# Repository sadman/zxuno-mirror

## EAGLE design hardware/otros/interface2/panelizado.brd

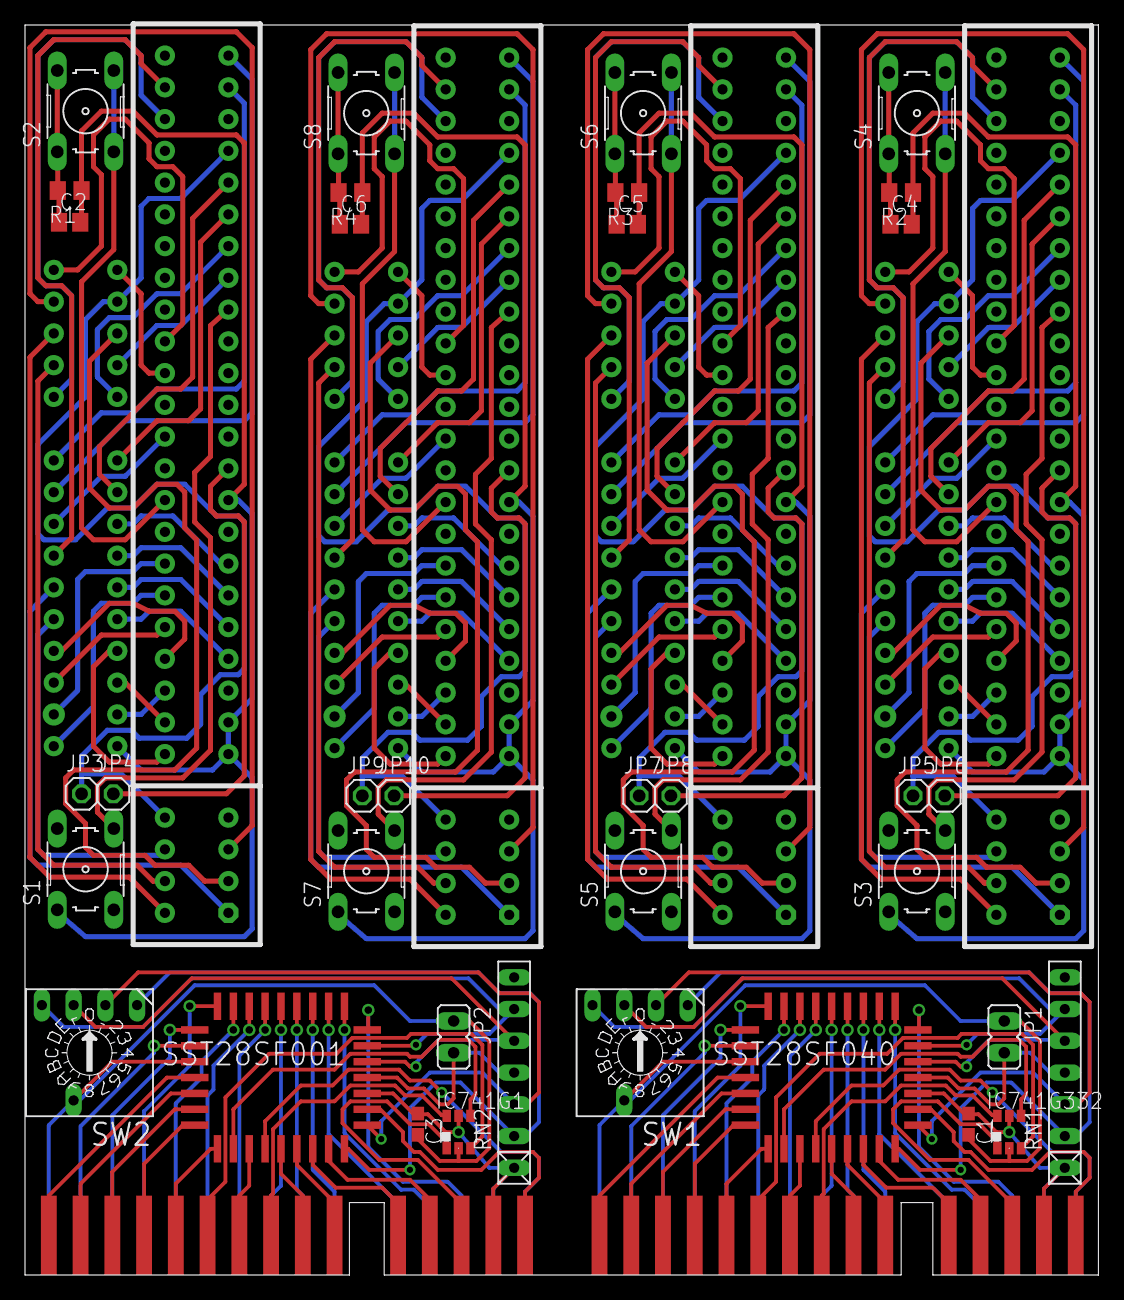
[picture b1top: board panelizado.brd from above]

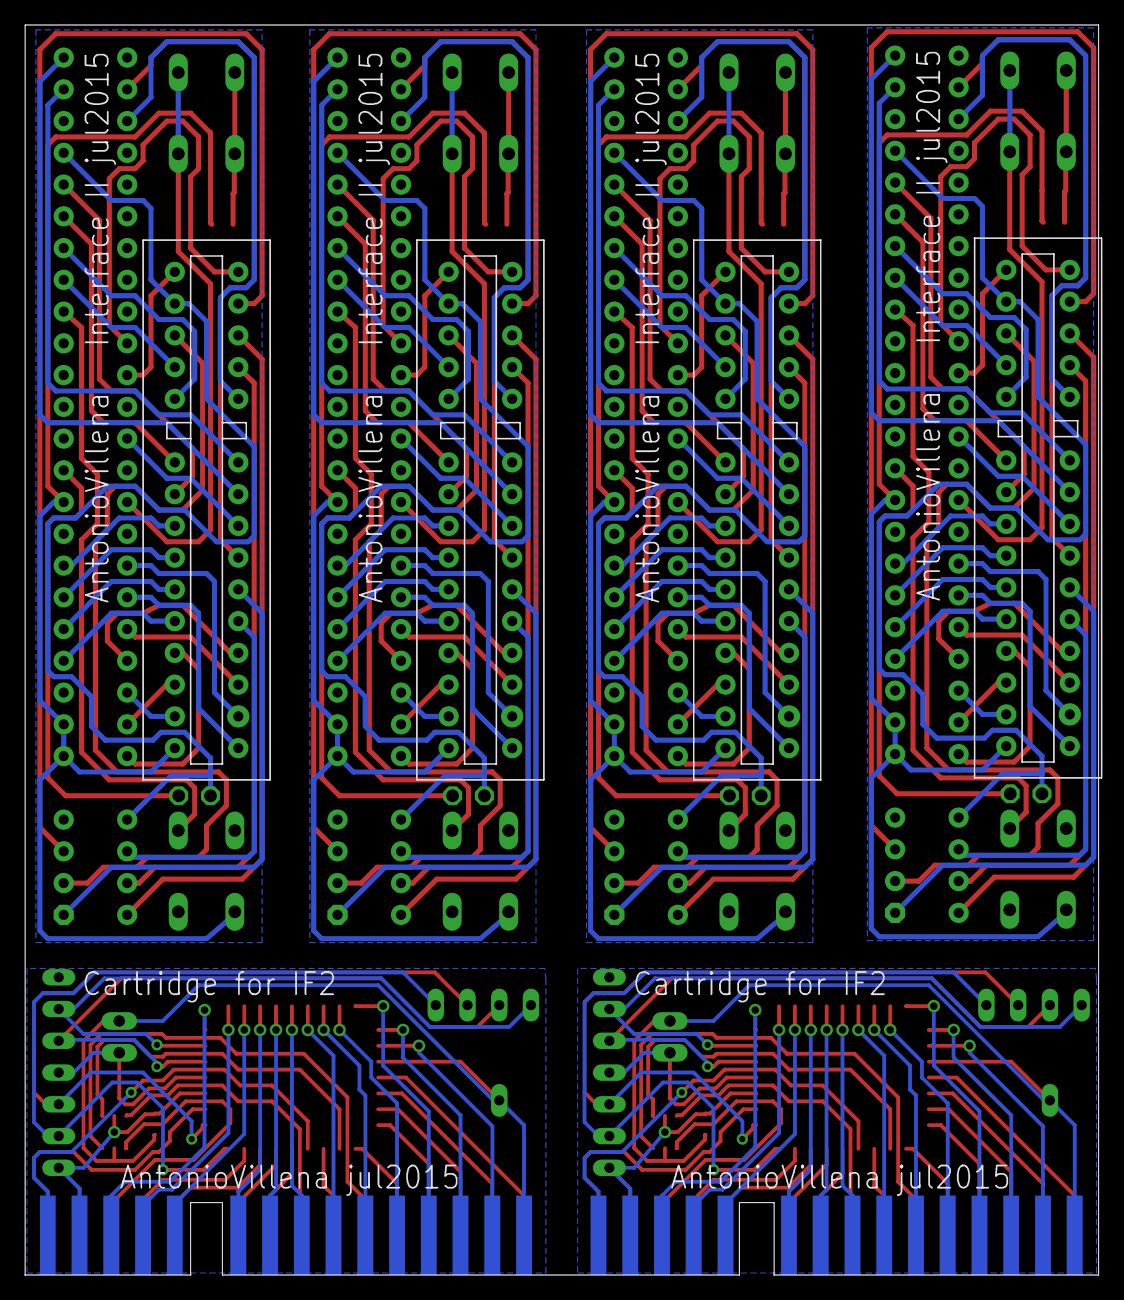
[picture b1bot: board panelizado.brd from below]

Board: 2 copper layers, 85.9 x 100.0 mm, 46 parts (4 on the bottom side), 206 nets.

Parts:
C1, C3: C0603
C2, C4, C5, C6: 4.7uF; C0805
IC741G1, IC741G332: DBV_R-PDSO-G6
JP1, JP2: JP1
JP3, JP4, JP5, JP6, JP7, JP8, JP9, JP10: 1X01
R1, R2, R3, R4: 1K; R0805
RN1, RN2: RN-7
S1, S2, S3, S4, S5, S6, S7, S8: B3F-10XX
SST28SF001, SST28SF040: PLCC32R
SW1, SW2: SW-C16
U$1, U$4: IF2BUS; BUS_CARTUCHO_IF2
U$2, U$6, U$8, U$10: ZX_CARTRIDGE
U$3, U$5, U$7, U$9: 2X28_SPE

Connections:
A0: SST28SF040.12, U$1.A0
A1: SST28SF040.11, U$1.A1
A2: SST28SF040.10, U$1.A2
A3: SST28SF040.9, U$1.A3
A4: SST28SF040.8, U$1.A4
A5: SST28SF040.7, U$1.A5
A6: SST28SF040.6, U$1.A6
A7: SST28SF040.5, U$1.A7
A8: SST28SF040.27, U$1.A8
A9: SST28SF040.26, U$1.A9
A10: SST28SF040.23, U$1.A10
A11: SST28SF040.25, U$1.A11
A12: SST28SF040.4, U$1.A12
A13: SST28SF040.28, U$1.A13
A14: IC741G332.3, U$1.A14
A15: IC741G332.1, U$1.A15
A16: U$2.A14, U$3.A1
A17: U$2.A10, U$3.B27
A18: U$2.A11, U$3.A28
A19: U$2.A9, U$3.A27
A20: U$2.A8, U$3.B26
A21: U$2.A13, U$3.B2
A22: U$2.A15, U$3.B1
A23: U$2.A0, U$3.A9
A24: U$2.A1, U$3.A10
A25: U$2.A2, U$3.A11
A26: U$2.A3, U$3.A12
A27: U$2.A4, U$3.A24
A28: U$2.A5, U$3.A23
A29: U$2.A6, U$3.A22
A30: U$2.A7, U$3.A21
A31: U$2.A12, U$3.A2
A32: SST28SF001.12, U$4.A0
A33: IC741G1.3, U$4.A14
A34: IC741G1.1, U$4.A15
A35: SST28SF001.11, U$4.A1
A36: SST28SF001.10, U$4.A2
A37: SST28SF001.9, U$4.A3
A38: SST28SF001.8, U$4.A4
A39: SST28SF001.7, U$4.A5
A40: SST28SF001.6, U$4.A6
A41: SST28SF001.5, U$4.A7
A42: SST28SF001.27, U$4.A8
A43: SST28SF001.26, U$4.A9
A44: SST28SF001.23, U$4.A10
A45: SST28SF001.25, U$4.A11
A46: SST28SF001.4, U$4.A12
A47: SST28SF001.28, U$4.A13
A48: U$5.A1, U$6.A14
A49: U$5.B27, U$6.A10
A50: U$5.A28, U$6.A11
A51: U$5.A27, U$6.A9
A52: U$5.B26, U$6.A8
A53: U$5.B2, U$6.A13
A54: U$5.B1, U$6.A15
A55: U$5.A9, U$6.A0
A56: U$5.A10, U$6.A1
A57: U$5.A11, U$6.A2
A58: U$5.A12, U$6.A3
A59: U$5.A24, U$6.A4
A60: U$5.A23, U$6.A5
A61: U$5.A22, U$6.A6
A62: U$5.A21, U$6.A7
A63: U$5.A2, U$6.A12
A64: U$7.A1, U$8.A14
A65: U$7.B27, U$8.A10
A66: U$7.A28, U$8.A11
A67: U$7.A27, U$8.A9
A68: U$7.B26, U$8.A8
A69: U$7.B2, U$8.A13
A70: U$7.B1, U$8.A15
A71: U$7.A9, U$8.A0
A72: U$7.A10, U$8.A1
A73: U$7.A11, U$8.A2
A74: U$7.A12, U$8.A3
A75: U$7.A24, U$8.A4
A76: U$7.A23, U$8.A5
A77: U$7.A22, U$8.A6
A78: U$7.A21, U$8.A7
A79: U$7.A2, U$8.A12
A80: U$9.A1, U$10.A14
A81: U$9.B27, U$10.A10
A82: U$9.A28, U$10.A11
A83: U$9.A27, U$10.A9
A84: U$9.B26, U$10.A8
A85: U$9.B2, U$10.A13
A86: U$9.B1, U$10.A15
A87: U$9.A9, U$10.A0
A88: U$9.A10, U$10.A1
A89: U$9.A11, U$10.A2
A90: U$9.A12, U$10.A3
A91: U$9.A24, U$10.A4
A92: U$9.A23, U$10.A5
A93: U$9.A22, U$10.A6
A94: U$9.A21, U$10.A7
A95: U$9.A2, U$10.A12
CS: IC741G332.4, SST28SF040.22
CS1: IC741G1.4, SST28SF001.22
D0: SST28SF040.13, U$1.D0
D1: SST28SF040.14, U$1.D1
D2: SST28SF040.15, U$1.D2
D3: SST28SF040.17, U$1.D3
D4: SST28SF040.18, U$1.D4
D5: SST28SF040.19, U$1.D5
D6: SST28SF040.20, U$1.D6
D7: SST28SF040.21, U$1.D7
D8: U$2.D3, U$3.B11
D9: U$2.D4, U$3.B12
D10: U$2.D5, U$3.B10
D11: U$2.D6, U$3.B9
D12: U$2.D7, U$3.B3
D13: U$2.D2, U$3.B8
D14: U$2.D1, U$3.B7
D15: U$2.D0, U$3.B6
D16: SST28SF001.13, U$4.D0
D17: SST28SF001.14, U$4.D1
D18: SST28SF001.15, U$4.D2
D19: SST28SF001.17, U$4.D3
D20: SST28SF001.18, U$4.D4
D21: SST28SF001.19, U$4.D5
D22: SST28SF001.20, U$4.D6
D23: SST28SF001.21, U$4.D7
D24: U$5.B11, U$6.D3
D25: U$5.B12, U$6.D4
D26: U$5.B10, U$6.D5
D27: U$5.B9, U$6.D6
D28: U$5.B3, U$6.D7
D29: U$5.B8, U$6.D2
D30: U$5.B7, U$6.D1
D31: U$5.B6, U$6.D0
D32: U$7.B11, U$8.D3
D33: U$7.B12, U$8.D4
D34: U$7.B10, U$8.D5
D35: U$7.B9, U$8.D6
D36: U$7.B3, U$8.D7
D37: U$7.B8, U$8.D2
D38: U$7.B7, U$8.D1
D39: U$7.B6, U$8.D0
D40: U$9.B11, U$10.D3
D41: U$9.B12, U$10.D4
D42: U$9.B10, U$10.D5
D43: U$9.B9, U$10.D6
D44: U$9.B3, U$10.D7
D45: U$9.B8, U$10.D2
D46: U$9.B7, U$10.D1
D47: U$9.B6, U$10.D0
GND: C1.2, IC741G332.2, JP1.1, SST28SF040.16, SW1.C, U$1.GND
GND1: C2.2, R1.1, S1.1, S1.2, U$2.GND, U$3.A6, U$3.A7, U$3.A14
GND2: C3.2, IC741G1.2, JP2.1, SST28SF001.16, SW2.C, U$4.GND
GND3: C4.2, R2.1, S3.1, S3.2, U$5.A6, U$5.A7, U$5.A14, U$6.GND
GND4: C5.2, R3.1, S5.1, S5.2, U$7.A6, U$7.A7, U$7.A14, U$8.GND
GND5: C6.2, R4.1, S7.1, S7.2, U$9.A6, U$9.A7, U$9.A14, U$10.GND
MREQ: IC741G332.6, U$1.MREQ
MREQ1: U$2.MREQ, U$3.B16
MREQ2: IC741G1.6, U$4.MREQ
MREQ3: U$5.B16, U$6.MREQ
MREQ4: U$7.B16, U$8.MREQ
MREQ5: U$9.B16, U$10.MREQ
unnamed: C2.1, R1.2, S2.1, S2.2
unnamed: JP1.2, RN1.4, SST28SF040.1
unnamed: RN1.3, SST28SF040.30, SW1.2
unnamed: RN1.5, SST28SF040.2, SW1.4
unnamed: RN1.6, SST28SF040.3, SW1.8
unnamed: RN1.2, SST28SF040.29, SW1.1
unnamed: JP2.2, RN2.4, SST28SF001.1
unnamed: RN2.3, SST28SF001.30, SW2.2
unnamed: RN2.5, SST28SF001.2, SW2.4
unnamed: RN2.6, SST28SF001.3, SW2.8
unnamed: RN2.2, SST28SF001.29, SW2.1
unnamed: JP4.1, U$3.A15
unnamed: C4.1, R2.2, S4.1, S4.2
unnamed: JP6.1, U$5.A15
unnamed: C5.1, R3.2, S6.1, S6.2
unnamed: JP8.1, U$7.A15
unnamed: C6.1, R4.2, S8.1, S8.2
unnamed: JP10.1, U$9.A15
NMI: S2.3, S2.4, U$3.B14
NMI1: S4.3, S4.4, U$5.B14
NMI2: S6.3, S6.4, U$7.B14
NMI3: S8.3, S8.4, U$9.B14
RD: SST28SF040.24, U$1.RD
RD1: U$2.RD, U$3.B18
RD2: SST28SF001.24, U$4.RD
RD3: U$5.B18, U$6.RD
RD4: U$7.B18, U$8.RD
RD5: U$9.B18, U$10.RD
RESET: S1.3, S1.4, U$3.A20
RESET1: S3.3, S3.4, U$5.A20
RESET2: S5.3, S5.4, U$7.A20
RESET3: S7.3, S7.4, U$9.A20
ROMCS: JP3.1, U$2.ROMCS, U$3.A25, U$3.B4
ROMCS1: JP5.1, U$5.A25, U$5.B4, U$6.ROMCS
ROMCS2: JP7.1, U$7.A25, U$7.B4, U$8.ROMCS
ROMCS3: JP9.1, U$9.A25, U$9.B4, U$10.ROMCS
VCC: C1.1, IC741G332.5, RN1.1, SST28SF040.32, U$1.ROMCS, U$1.VCC
VCC1: U$2.+5V, U$3.A3
VCC2: C3.1, IC741G1.5, RN2.1, SST28SF001.32, U$4.ROMCS, U$4.VCC
VCC3: U$5.A3, U$6.+5V
VCC4: U$7.A3, U$8.+5V
VCC5: U$9.A3, U$10.+5V
WR: SST28SF040.31, U$1.WR
WR1: U$2.WR, U$3.B19
WR2: SST28SF001.31, U$4.WR
WR3: U$5.B19, U$6.WR
WR4: U$7.B19, U$8.WR
WR5: U$9.B19, U$10.WR

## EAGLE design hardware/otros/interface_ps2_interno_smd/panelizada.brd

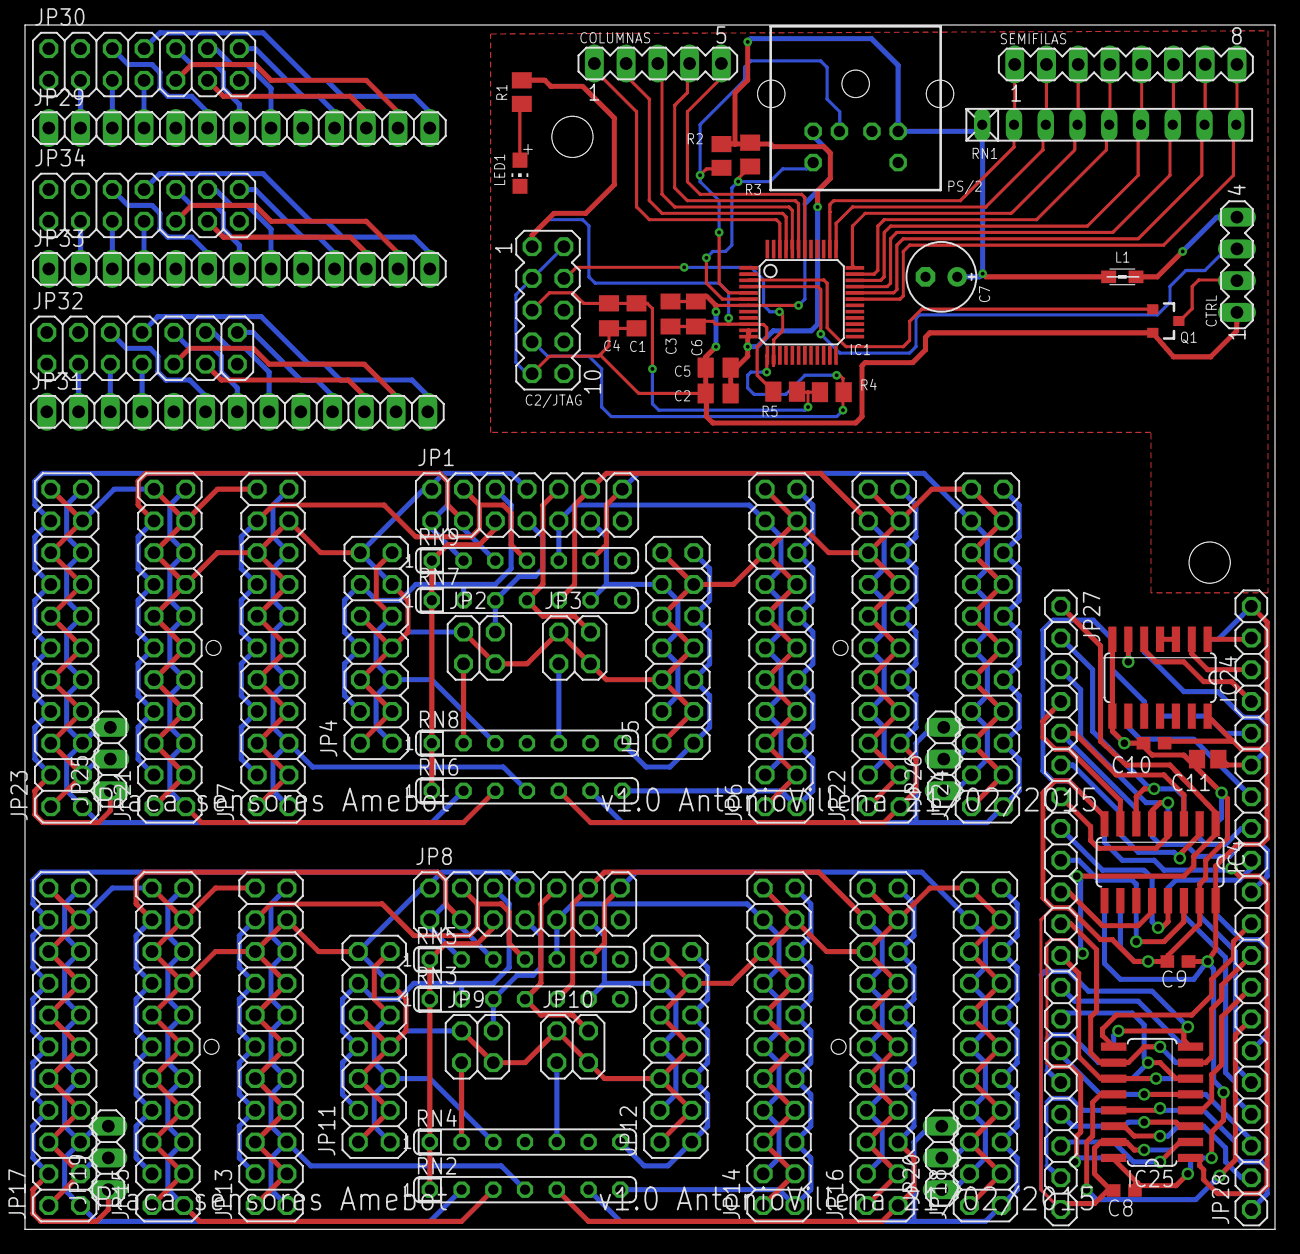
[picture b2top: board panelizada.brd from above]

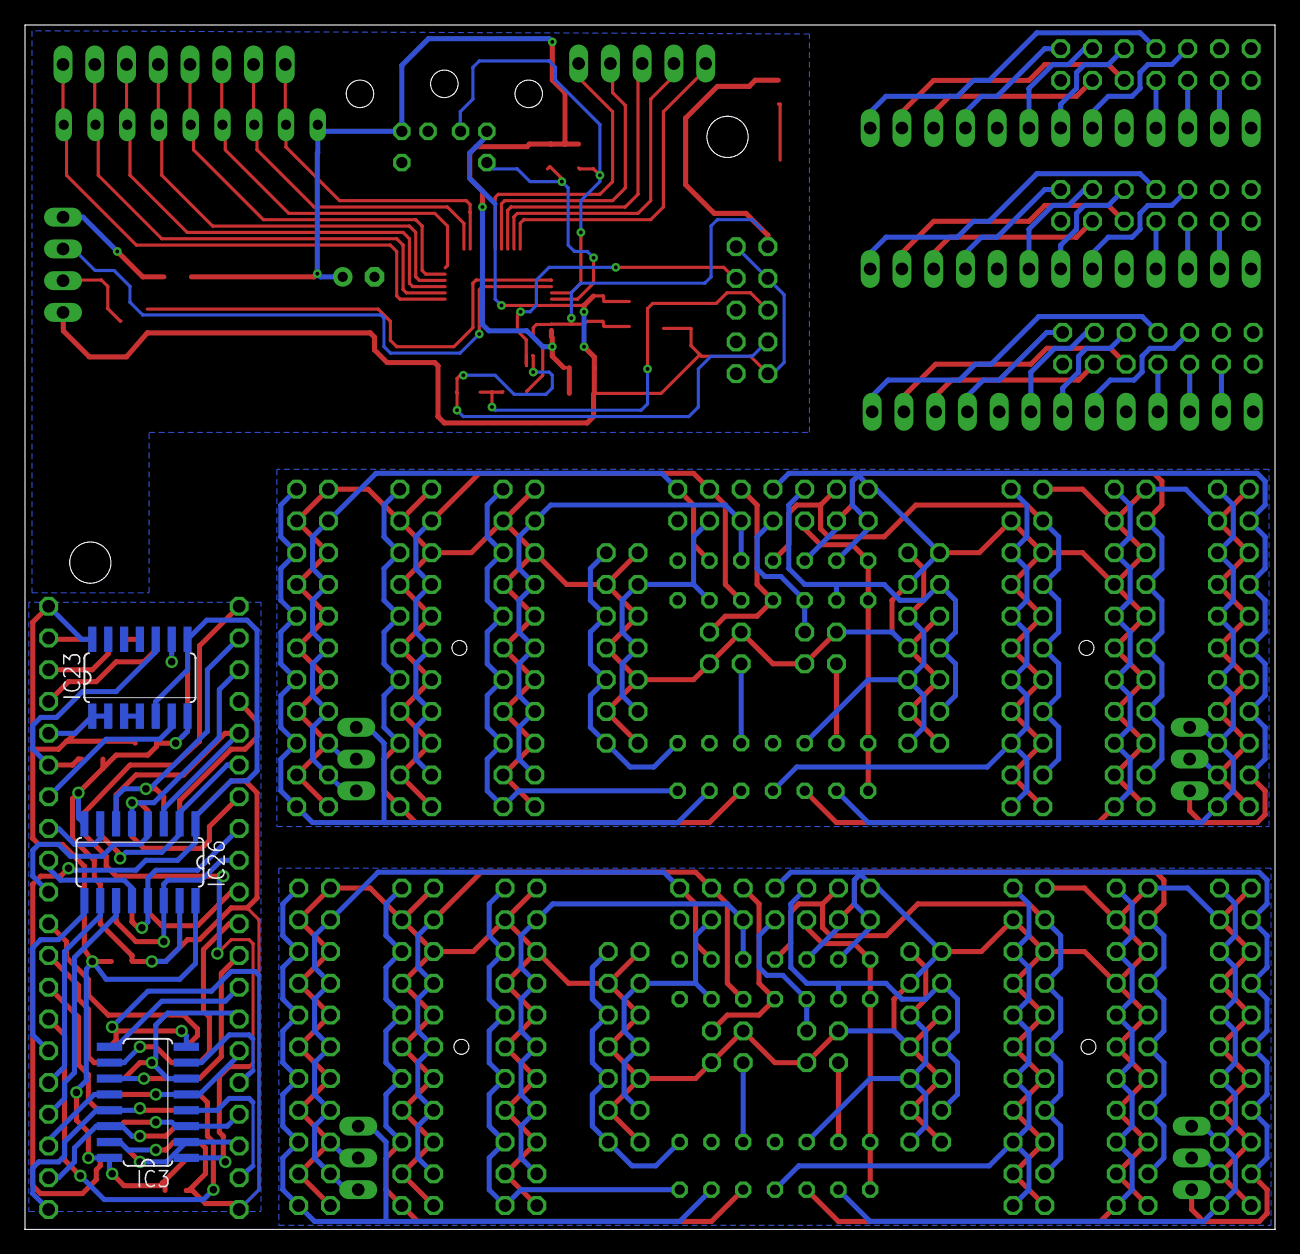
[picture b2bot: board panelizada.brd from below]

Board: 2 copper layers, 100.0 x 96.3 mm, 74 parts (3 on the bottom side), 144 nets.

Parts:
C1, C2, C3: 100nF; C0805K
C2/JTAG: MA05-2
C4, C5, C6: 1uF; C0805K
C7: 100uF; E2,5-6E
C8, C9: C0603
C10: 100n; C0603
C11: C0805
COLUMNAS: MA05-1
CTRL: MA04-1
IC1: C8051F340; TQFP48
IC3, IC4, IC25, IC26: 74*157; SO16
IC23: 74LS32D; SO14
IC24: 74LS00D; SO14
JP1, JP4, JP5, JP8, JP11, JP12, JP30, JP32, JP34: 2X07
JP2, JP3, JP9, JP10: 2X02
JP6, JP7, JP13, JP14, JP15, JP16, JP17, JP18, JP21, JP22, JP23, JP24: 2X11
JP19, JP20, JP25, JP26: 1X03
JP27, JP28: 1X20
JP29, JP31, JP33: 1X13
L1: 0805
LED1: CHIP-LED0805
PS/2: SSV-BC06
Q1: 2N2222; SOT23-3
R1: 470; M0805
R2, R3: 10K; M0805
R4, R5: 1K; M0805
RN1: RN-9
RN2, RN3, RN4, RN5, RN6, RN7, RN8, RN9: SIL7
SEMIFILAS: MA08-1

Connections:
3.3V: JP8.5, RN2.1, RN3.1, RN4.1, RN5.1
3.3V1: JP1.5, RN6.1, RN7.1, RN8.1, RN9.1
3A: IC26.11, JP28.4
3B: IC26.10, JP28.5
5VDC: C2.1, C5.1, C7.+, IC1.11, IC1.12, L1.2, PS/2.4, R2.2, R3.2, RN1.1
A0: IC4.6, IC26.6, JP27.2
A1: IC4.3, IC26.3, JP27.5
A2: IC4.13, IC26.13, JP27.8
A3: IC3.10, IC25.10, JP27.11
A4: IC3.6, IC25.6, JP27.14
A5: IC3.3, IC25.3, JP27.17
A6: IC3.13, IC25.13, JP28.1
A7: IC4.5, IC26.5, JP27.3
A8: IC4.2, IC26.2, JP27.6
A9: IC4.14, IC26.14, JP27.9
A10: IC3.11, IC25.11, JP27.12
A11: IC3.5, IC25.5, JP27.15
A12: IC3.2, IC25.2, JP27.18
A13: IC3.14, IC25.14, JP28.2
A15: IC24.5, JP28.17
CASL: IC23.6, JP28.14
D0: COLUMNAS.1, IC1.46
D1: COLUMNAS.2, IC1.45
D2: COLUMNAS.3, IC1.44
D3: COLUMNAS.4, IC1.43
D4: COLUMNAS.5, IC1.42
DMA0: IC4.7, JP27.4
DMA1: IC4.4, JP27.7
DMA2: IC4.12, JP27.10
DMA3: IC3.9, JP27.13
DMA4: IC3.7, JP27.16
DMA5: IC3.4, JP27.19
DMA6: IC3.12, JP28.3
DRASLL: IC3.1, IC4.1, JP27.1
GND: JP1.2, JP1.8, JP1.13, JP2.2, JP2.3, JP3.2, JP3.3, JP4.2, JP4.3, JP4.6, JP4.7, JP4.10, JP4.11, JP4.14, JP5.2, JP5.3, JP5.6, JP5.7, JP5.10, JP5.11, JP5.14, JP6.2, JP6.3, JP6.6, JP6.7, JP6.10, JP6.11, JP6.14, JP6.15, JP6.18, JP6.19, JP6.22, JP7.2, JP7.3, JP7.6, JP7.7, JP7.10, JP7.11, JP7.14, JP7.15, JP7.18, JP7.19, JP7.22, JP21.2, JP21.3, JP21.6, JP21.7, JP21.10, JP21.11, JP21.14, JP21.15, JP21.18, JP21.19, JP21.22, JP22.2, JP22.3, JP22.6, JP22.7, JP22.10, JP22.11, JP22.14, JP22.15, JP22.18, JP22.19, JP22.22, JP23.2, JP23.3, JP23.6, JP23.7, JP23.10, JP23.11, JP23.14, JP23.15, JP23.18, JP23.19, JP23.22, JP24.2, JP24.3, JP24.6, JP24.7, JP24.10, JP24.11, JP24.14, JP24.15, JP24.18, JP24.19, JP24.22, JP25.2, JP26.2
GND1: C1.2, C2.2, C2/JTAG.2, C2/JTAG.3, C2/JTAG.9, C3.2, C4.2, C5.2, C6.2, C7.-, CTRL.1, IC1.7, LED1.C, PS/2.3, Q1.2
GND2: JP8.2, JP8.8, JP8.13, JP9.2, JP9.3, JP10.2, JP10.3, JP11.2, JP11.3, JP11.6, JP11.7, JP11.10, JP11.11, JP11.14, JP12.2, JP12.3, JP12.6, JP12.7, JP12.10, JP12.11, JP12.14, JP13.2, JP13.3, JP13.6, JP13.7, JP13.10, JP13.11, JP13.14, JP13.15, JP13.18, JP13.19, JP13.22, JP14.2, JP14.3, JP14.6, JP14.7, JP14.10, JP14.11, JP14.14, JP14.15, JP14.18, JP14.19, JP14.22, JP15.2, JP15.3, JP15.6, JP15.7, JP15.10, JP15.11, JP15.14, JP15.15, JP15.18, JP15.19, JP15.22, JP16.2, JP16.3, JP16.6, JP16.7, JP16.10, JP16.11, JP16.14, JP16.15, JP16.18, JP16.19, JP16.22, JP17.2, JP17.3, JP17.6, JP17.7, JP17.10, JP17.11, JP17.14, JP17.15, JP17.18, JP17.19, JP17.22, JP18.2, JP18.3, JP18.6, JP18.7, JP18.10, JP18.11, JP18.14, JP18.15, JP18.18, JP18.19, JP18.22, JP19.2, JP20.2
GND3: C8.2, C9.2, C10.2, C11.2, IC3.8, IC3.15, IC4.8, IC4.15, IC23.7, IC24.7, IC25.8, IC25.15, IC26.8, IC26.15, JP27.20
IORQULA: CTRL.3, IC1.4
KBD_CLK: IC1.6, PS/2.5, R3.1
KBD_DATA: IC1.5, PS/2.1, R2.1
MA0: IC26.7, JP28.13
MA1: IC26.12, JP28.12
MA2: IC26.4, JP28.11
MA3: IC25.9, JP28.10
MA4: IC25.7, JP28.9
MA5: IC25.4, JP28.8
MA6: IC25.12, JP28.7
MA7: IC26.9, JP28.6
MREQ: IC23.1, IC23.2, JP28.16
MREQDL: C11.1, IC23.10, JP28.15
unnamed: JP22.1, JP22.5, JP22.9, JP22.13, JP22.17, JP22.21, RN6.5
unnamed: JP2.1, RN8.2
unnamed: JP7.1, JP7.5, JP7.9, JP7.13, JP7.17, JP7.21, RN6.4
unnamed: JP4.1, JP4.5, JP4.9, JP4.13, RN8.3
unnamed: JP5.1, JP5.5, JP5.9, JP5.13, RN8.7
unnamed: JP3.1, RN8.5
unnamed: JP6.1, JP6.5, JP6.9, JP6.13, JP6.17, JP6.21, RN6.7
unnamed: JP24.1, JP24.5, JP24.9, JP24.13, JP24.17, JP24.21, JP26.3, RN6.6
unnamed: JP23.1, JP23.5, JP23.9, JP23.13, JP23.17, JP23.21, JP25.3, RN6.2
unnamed: JP21.1, JP21.5, JP21.9, JP21.13, JP21.17, JP21.21, RN6.3
unnamed: IC24.3, IC24.4
unnamed: IC23.9, IC24.6
unnamed: IC23.3, IC23.4
unnamed: IC23.5, IC23.8, IC25.1, IC26.1
unnamed: JP29.2, JP30.3
unnamed: JP29.3, JP30.5
unnamed: JP29.4, JP30.7
unnamed: C1.1, C2/JTAG.5, C4.1, R4.2, R5.2
unnamed: LED1.A, R1.2
unnamed: C2/JTAG.7, IC1.13, R4.1
unnamed: C2/JTAG.4, IC1.14
unnamed: CTRL.2, Q1.3
unnamed: CTRL.4, L1.1
unnamed: JP13.1, JP13.5, JP13.9, JP13.13, JP13.17, JP13.21, RN2.4
unnamed: JP15.1, JP15.5, JP15.9, JP15.13, JP15.17, JP15.21, RN2.3
unnamed: JP17.1, JP17.5, JP17.9, JP17.13, JP17.17, JP17.21, JP19.3, RN2.2
unnamed: JP16.1, JP16.5, JP16.9, JP16.13, JP16.17, JP16.21, RN2.5
unnamed: JP9.1, RN4.2
unnamed: JP11.1, JP11.5, JP11.9, JP11.13, RN4.3
unnamed: JP12.1, JP12.5, JP12.9, JP12.13, RN4.7
unnamed: JP10.1, RN4.5
unnamed: JP14.1, JP14.5, JP14.9, JP14.13, JP14.17, JP14.21, RN2.7
unnamed: JP18.1, JP18.5, JP18.9, JP18.13, JP18.17, JP18.21, JP20.3, RN2.6
unnamed: JP29.12, JP30.9
unnamed: JP29.11, JP30.11
unnamed: JP29.10, JP30.14
unnamed: JP29.8, JP30.12
unnamed: JP29.6, JP30.6
unnamed: JP29.7, JP30.10
unnamed: JP29.13, JP30.8
unnamed: JP31.2, JP32.3
unnamed: JP31.3, JP32.5
unnamed: JP31.4, JP32.7
unnamed: JP31.12, JP32.9
unnamed: JP31.11, JP32.11
unnamed: JP31.10, JP32.14
unnamed: JP31.8, JP32.12
unnamed: JP31.6, JP32.6
unnamed: JP31.7, JP32.10
unnamed: JP31.13, JP32.8
unnamed: JP33.2, JP34.3
unnamed: JP33.3, JP34.5
unnamed: JP33.4, JP34.7
unnamed: JP33.12, JP34.9
unnamed: JP33.11, JP34.11
unnamed: JP33.10, JP34.14
unnamed: JP33.8, JP34.12
unnamed: JP33.6, JP34.6
unnamed: JP33.7, JP34.10
unnamed: JP33.13, JP34.8
RD: IC24.2, JP28.18
RESET: IC1.3, Q1.1
SEN1: JP8.1, JP17.4, JP17.8, JP17.12, JP17.16, JP17.20, JP19.1, RN5.2
SEN2: JP8.3, JP15.4, JP15.8, JP15.12, JP15.16, JP15.20, RN5.3
SEN3: JP8.7, JP9.4, RN3.3
SEN4: JP8.9, JP14.4, JP14.8, JP14.12, JP14.16, JP14.20, RN5.5
SEN5: JP8.11, JP12.4, JP12.8, JP12.12, RN3.6
SEN6: JP8.4, JP13.4, JP13.8, JP13.12, JP13.16, JP13.20, RN5.4
SEN7: JP8.6, JP11.4, JP11.8, JP11.12, RN3.2
SEN8: JP8.10, JP10.4, RN3.4
SEN9: JP8.12, JP16.4, JP16.8, JP16.12, JP16.16, JP16.20, RN3.5
SEN10: JP8.14, JP18.4, JP18.8, JP18.12, JP18.16, JP18.20, JP20.1, RN5.6
SEN11: JP1.1, JP23.4, JP23.8, JP23.12, JP23.16, JP23.20, JP25.1, RN9.2
SEN12: JP1.3, JP21.4, JP21.8, JP21.12, JP21.16, JP21.20, RN9.3
SEN13: JP1.4, JP7.4, JP7.8, JP7.12, JP7.16, JP7.20, RN9.4
SEN14: JP1.6, JP4.4, JP4.8, JP4.12, RN7.2
SEN15: JP1.10, JP3.4, RN7.4
SEN16: JP1.12, JP22.4, JP22.8, JP22.12, JP22.16, JP22.20, RN7.5
SEN17: JP1.14, JP24.4, JP24.8, JP24.12, JP24.16, JP24.20, JP26.1, RN9.6
SEN18: JP1.7, JP2.4, RN7.3
SEN19: JP1.9, JP6.4, JP6.8, JP6.12, JP6.16, JP6.20, RN9.5
SEN20: JP1.11, JP5.4, JP5.8, JP5.12, RN7.6
SF1: IC1.38, RN1.2, SEMIFILAS.1
SF2: IC1.37, RN1.3, SEMIFILAS.2
SF3: IC1.36, RN1.4, SEMIFILAS.3
SF4: IC1.35, RN1.5, SEMIFILAS.4
SF5: IC1.34, RN1.6, SEMIFILAS.5
SF6: IC1.33, RN1.7, SEMIFILAS.6
SF7: IC1.32, RN1.8, SEMIFILAS.7
SF8: IC1.31, RN1.9, SEMIFILAS.8
VCC: C8.1, C9.1, C10.1, IC3.16, IC4.16, IC23.14, IC24.14, IC25.16, IC26.16, JP28.20
VDD: C2/JTAG.1, C3.1, C6.1, IC1.10, R1.1, R5.1
WR: IC24.1, JP28.19

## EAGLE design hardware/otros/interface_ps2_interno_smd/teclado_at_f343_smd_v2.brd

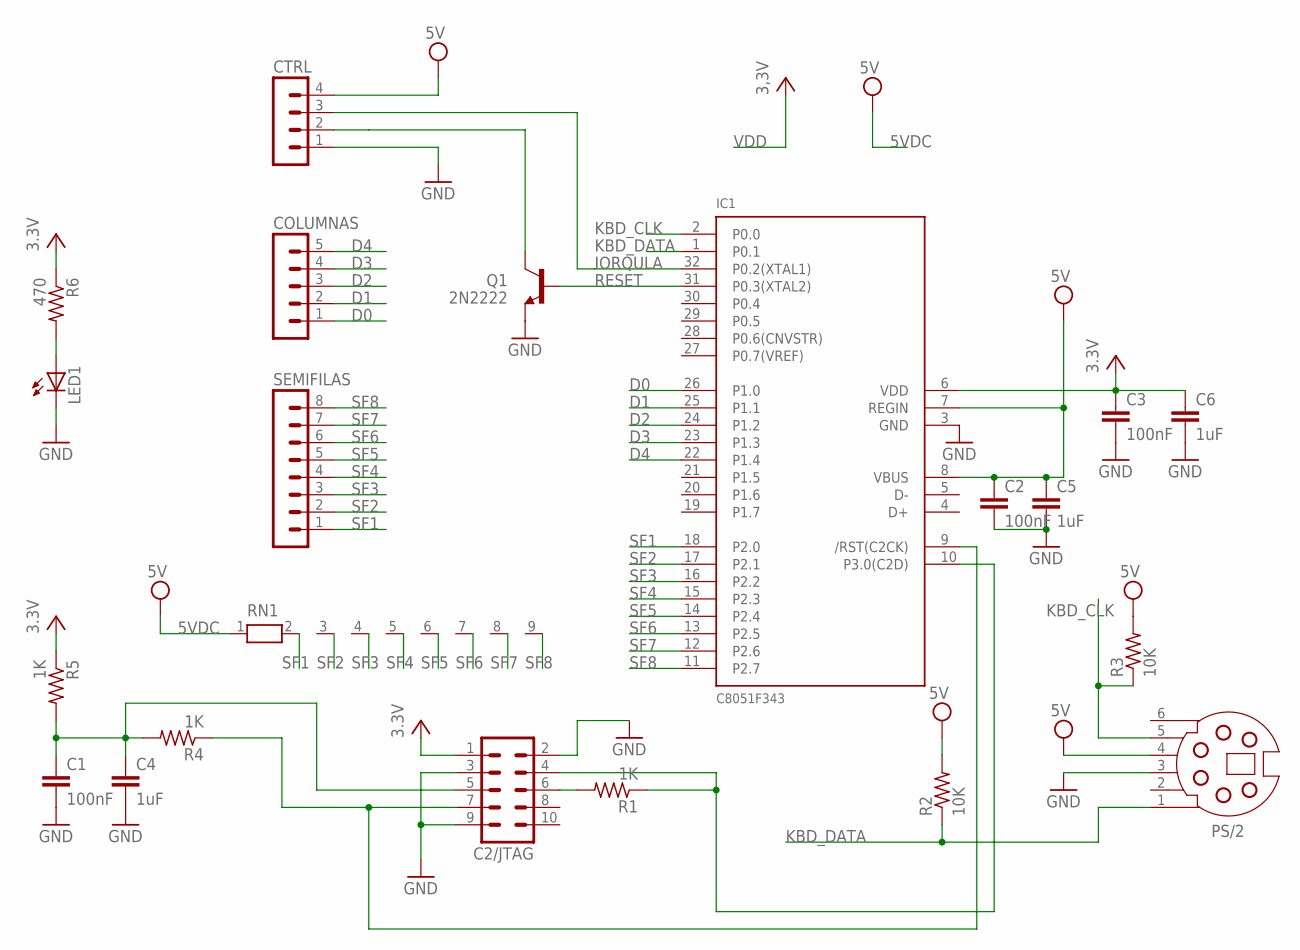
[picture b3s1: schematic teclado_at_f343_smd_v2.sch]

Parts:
C1, C2, C3: 100nF; C0805K
C2/JTAG: MA05-2
C4, C5, C6: 1uF; C0805K
COLUMNAS: MA05-1
CTRL: MA04-1
IC1: C8051F343; TQFP32-08
LED1: LEDCHIP-LED0805; CHIP-LED0805
PS/2: SSV-G06; SSV-BC06
Q1: 2N2222; SOT23-3
R1, R4, R5: 1K; M0805
R2, R3: 10K; M0805
R6: 470; M0805
RN1: RN08; RN-9
SEMIFILAS: MA08-1

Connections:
5VDC: C2.1, C5.1, CTRL.4, IC1.7 (REGIN), IC1.8 (VBUS), PS/2.4, R2.2, R3.2, RN1.1
D0: COLUMNAS.1, IC1.26 (P1.0)
D1: COLUMNAS.2, IC1.25 (P1.1)
D2: COLUMNAS.3, IC1.24 (P1.2)
D3: COLUMNAS.4, IC1.23 (P1.3)
D4: COLUMNAS.5, IC1.22 (P1.4)
GND: C1.2, C2.2, C2/JTAG.2, C2/JTAG.3, C2/JTAG.9, C3.2, C4.2, C5.2, C6.2, CTRL.1, IC1.3 (GND), LED1.C, PS/2.3, Q1.2 (E)
IORQULA: CTRL.3, IC1.32 (P0.2(XTAL1))
KBD_CLK: IC1.2 (P0.0), PS/2.5, R3.1
KBD_DATA: IC1.1 (P0.1), PS/2.1, R2.1
unnamed: C2/JTAG.7, IC1.9 (/RST(C2CK)), R4.1
unnamed: LED1.A, R6.2
unnamed: C1.1, C2/JTAG.5, C4.1, R4.2, R5.2
unnamed: C2/JTAG.4, IC1.10 (P3.0(C2D)), R1.1
unnamed: C2/JTAG.6, R1.2
unnamed: CTRL.2, Q1.3 (C)
RESET: IC1.31 (P0.3(XTAL2)), Q1.1 (B)
SF1: IC1.18 (P2.0), RN1.2, SEMIFILAS.1
SF2: IC1.17 (P2.1), RN1.3, SEMIFILAS.2
SF3: IC1.16 (P2.2), RN1.4, SEMIFILAS.3
SF4: IC1.15 (P2.3), RN1.5, SEMIFILAS.4
SF5: IC1.14 (P2.4), RN1.6, SEMIFILAS.5
SF6: IC1.13 (P2.5), RN1.7, SEMIFILAS.6
SF7: IC1.12 (P2.6), RN1.8, SEMIFILAS.7
SF8: IC1.11 (P2.7), RN1.9, SEMIFILAS.8
VDD: C2/JTAG.1, C3.1, C6.1, IC1.6 (VDD), R5.1, R6.1

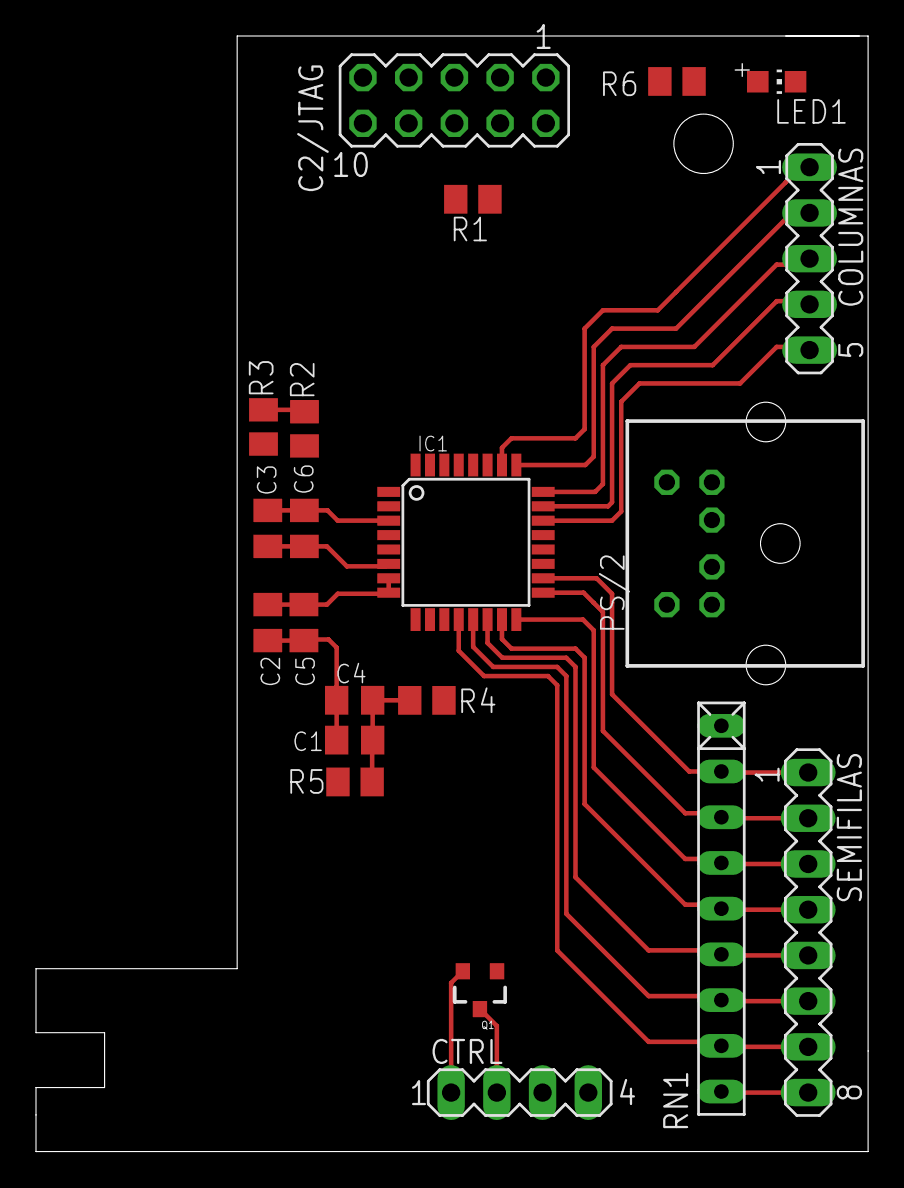
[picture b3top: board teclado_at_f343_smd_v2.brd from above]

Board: 2 copper layers, 46.2 x 62.0 mm, 21 parts (0 on the bottom side), 26 nets.

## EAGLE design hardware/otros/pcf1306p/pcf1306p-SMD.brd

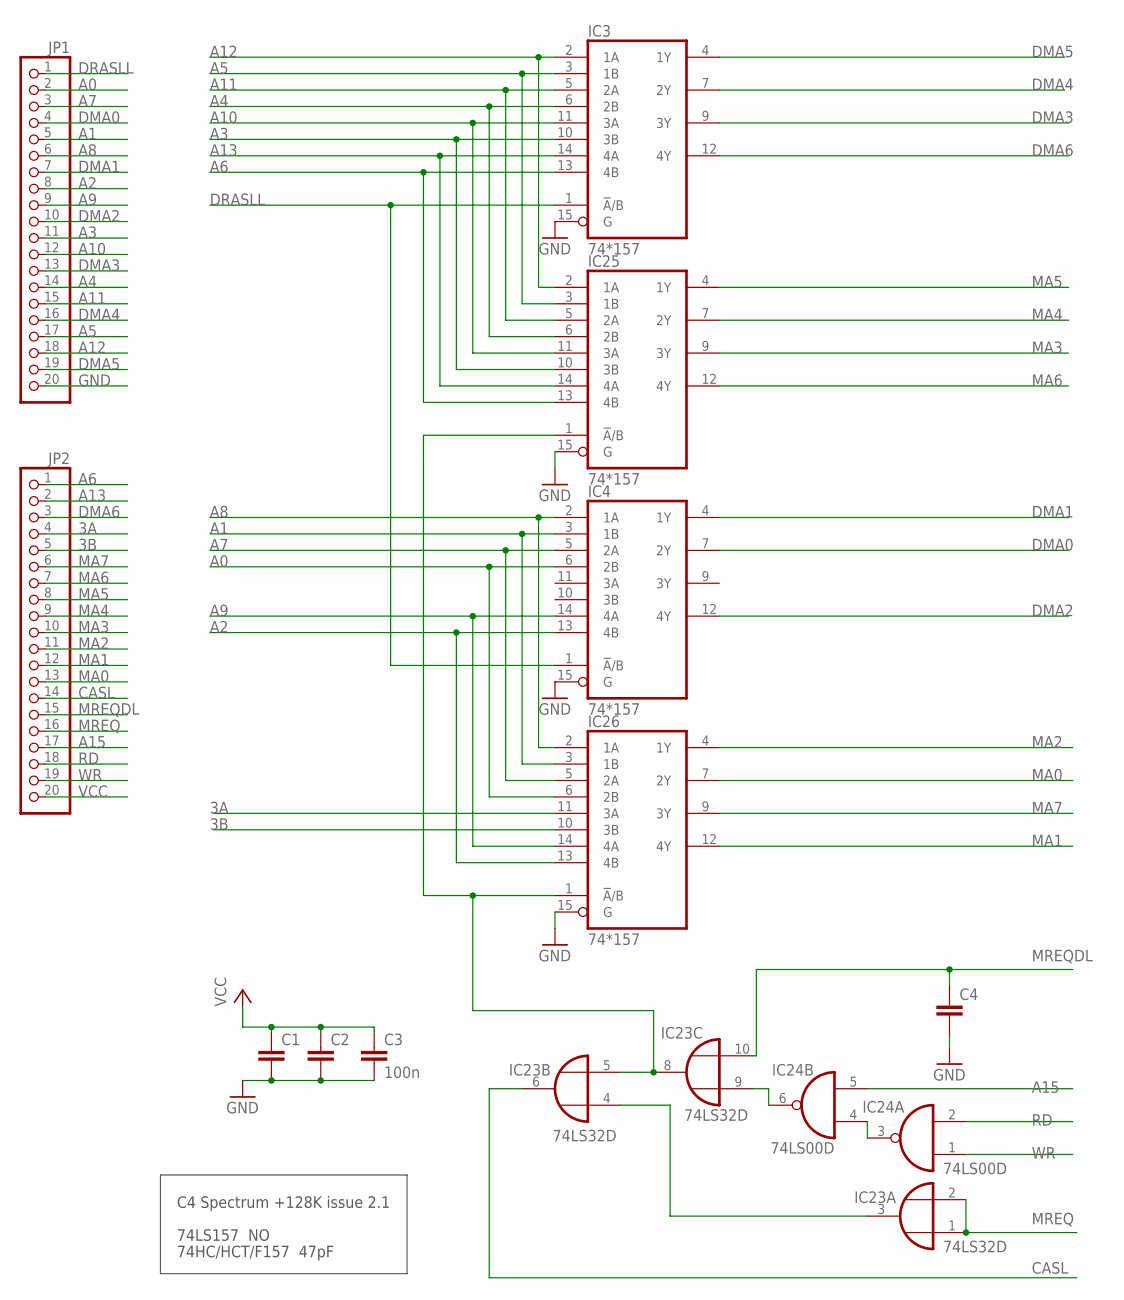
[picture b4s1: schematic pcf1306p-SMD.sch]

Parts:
C1, C2: C-EUC0603; C0603
C3: 100n; C0603
C4: C-EUC0805; C0805
IC3, IC4, IC25, IC26: 74*157; SO16
IC23: 74LS32D; SO14
IC24: 74LS00D; SO14
JP1, JP2: PINHD-1X20; 1X20

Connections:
3A: IC26.11 (3A), JP2.4
3B: IC26.10 (3B), JP2.5
A0: IC4.6 (2B), IC26.6 (2B), JP1.2
A1: IC4.3 (1B), IC26.3 (1B), JP1.5
A2: IC4.13 (4B), IC26.13 (4B), JP1.8
A3: IC3.10 (3B), IC25.10 (3B), JP1.11
A4: IC3.6 (2B), IC25.6 (2B), JP1.14
A5: IC3.3 (1B), IC25.3 (1B), JP1.17
A6: IC3.13 (4B), IC25.13 (4B), JP2.1
A7: IC4.5 (2A), IC26.5 (2A), JP1.3
A8: IC4.2 (1A), IC26.2 (1A), JP1.6
A9: IC4.14 (4A), IC26.14 (4A), JP1.9
A10: IC3.11 (3A), IC25.11 (3A), JP1.12
A11: IC3.5 (2A), IC25.5 (2A), JP1.15
A12: IC3.2 (1A), IC25.2 (1A), JP1.18
A13: IC3.14 (4A), IC25.14 (4A), JP2.2
A15: IC24.5 (I1), JP2.17
CASL: IC23.6 (O), JP2.14
DMA0: IC4.7 (2Y), JP1.4
DMA1: IC4.4 (1Y), JP1.7
DMA2: IC4.12 (4Y), JP1.10
DMA3: IC3.9 (3Y), JP1.13
DMA4: IC3.7 (2Y), JP1.16
DMA5: IC3.4 (1Y), JP1.19
DMA6: IC3.12 (4Y), JP2.3
DRASLL: IC3.1 (!A!/B), IC4.1 (!A!/B), JP1.1
GND: C1.2, C2.2, C3.2, C4.2, IC3.8 (GND), IC3.15 (G), IC4.8 (GND), IC4.15 (G), IC23.7 (GND), IC24.7 (GND), IC25.8 (GND), IC25.15 (G), IC26.8 (GND), IC26.15 (G), JP1.20
MA0: IC26.7 (2Y), JP2.13
MA1: IC26.12 (4Y), JP2.12
MA2: IC26.4 (1Y), JP2.11
MA3: IC25.9 (3Y), JP2.10
MA4: IC25.7 (2Y), JP2.9
MA5: IC25.4 (1Y), JP2.8
MA6: IC25.12 (4Y), JP2.7
MA7: IC26.9 (3Y), JP2.6
MREQ: IC23.1 (I0), IC23.2 (I1), JP2.16
MREQDL: C4.1, IC23.10 (I1), JP2.15
unnamed: IC23.3 (O), IC23.4 (I0)
unnamed: IC23.5 (I1), IC23.8 (O), IC25.1 (!A!/B), IC26.1 (!A!/B)
unnamed: IC24.3 (O), IC24.4 (I0)
unnamed: IC23.9 (I0), IC24.6 (O)
RD: IC24.2 (I1), JP2.18
VCC: C1.1, C2.1, C3.1, IC3.16 (VCC), IC4.16 (VCC), IC23.14 (VCC), IC24.14 (VCC), IC25.16 (VCC), IC26.16 (VCC), JP2.20
WR: IC24.1 (I0), JP2.19

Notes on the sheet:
74LS157 NO
74HC/HCT/F157 47pF
C4 Spectrum +128K issue 2.1

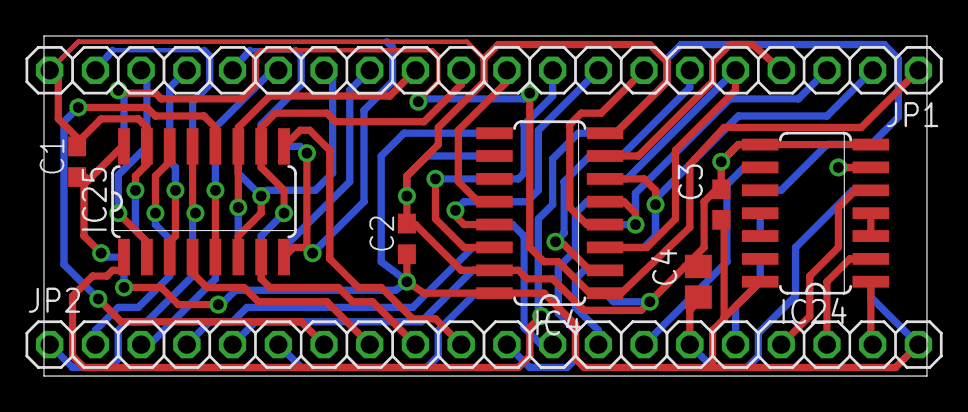
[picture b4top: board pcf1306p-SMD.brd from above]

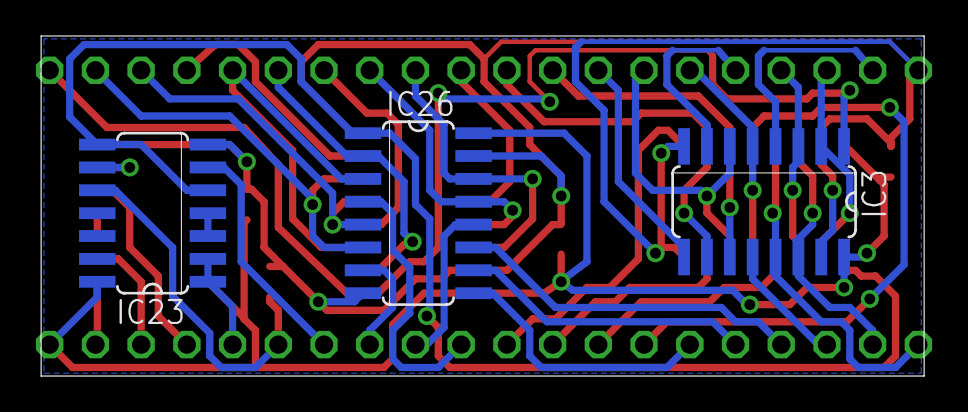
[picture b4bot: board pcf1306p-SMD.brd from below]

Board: 2 copper layers, 49.1 x 18.9 mm, 12 parts (3 on the bottom side), 44 nets.

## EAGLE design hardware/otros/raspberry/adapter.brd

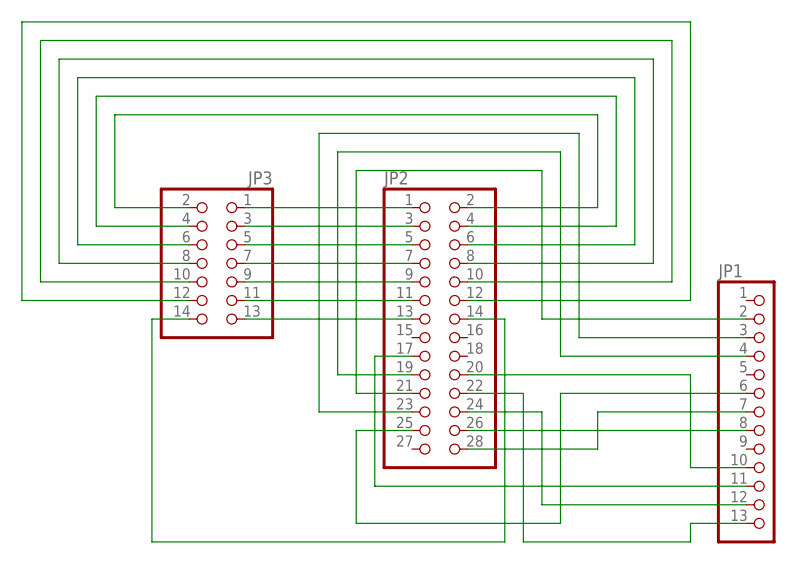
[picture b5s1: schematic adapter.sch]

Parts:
JP1: PINHD-1X13; 1X13
JP2: PINHD-2X14; 2X14
JP3: PINHD-2X7; 2X07

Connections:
unnamed: JP1.3, JP2.23
unnamed: JP1.4, JP2.19
unnamed: JP1.12, JP2.24
unnamed: JP1.7, JP2.28
unnamed: JP1.10, JP2.20
unnamed: JP1.8, JP2.26
unnamed: JP1.2, JP2.21
unnamed: JP1.6, JP2.25
unnamed: JP2.1, JP3.1
unnamed: JP2.3, JP3.3
unnamed: JP2.5, JP3.5
unnamed: JP2.7, JP3.7
unnamed: JP2.9, JP3.9
unnamed: JP2.11, JP3.11
unnamed: JP2.13, JP3.13
unnamed: JP2.2, JP3.2
unnamed: JP2.4, JP3.4
unnamed: JP2.6, JP3.6
unnamed: JP2.8, JP3.8
unnamed: JP2.10, JP3.10
unnamed: JP2.12, JP3.12
unnamed: JP2.14, JP3.14
unnamed: JP1.11, JP2.17
unnamed: JP1.13, JP2.22

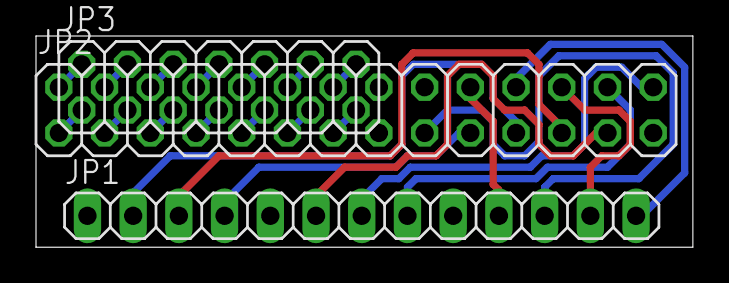
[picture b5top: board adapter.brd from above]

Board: 2 copper layers, 36.5 x 11.7 mm, 3 parts (0 on the bottom side), 24 nets.

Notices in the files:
hardware/otros/interface_ps2_interno_smd/panelizada.brd:
(C)2006-2015 McLeod/IdeaFix
parts and their libraries:
wuerth-elektronik: Copyright: Würth Elektronik eiSos
SparkFun-Connectors: Licensing: Creative Commons ShareAlike 4.0 International - https://creativecommons.org/licenses/by-sa/4.0
